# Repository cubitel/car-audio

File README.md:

Car Audio
=========

USB audio amplifier that turns android-based tablet into
full-featured automotive head unit.

#### Interfaces
- USB device interface for tablet
- USB host interface
- 4x45W digital class D automotive audio amplifier
- 2 CAN interfaces
- 100Base-T1 automotive ethernet interface
- Analog input for steering wheel keys
- FM radio available as separate shield

Amplifier acts as USB multifunctional device with ethernet and audio interfaces.

USB ethernet interface is used for configuration and control.
Interface has static IP address 192.168.91.11/24.

Hardware
--------

KiCad pcb files located in _pcb_ directory.
They include main amplifier board and FM tuner shield.

Software
--------

There is bootloader stub and main firmware.

#### Requirements

To install build tools in ubuntu:
```
sudo apt-get install gcc-arm-none-eabi dfu-util openssl protobuf-compiler python-protobuf
```

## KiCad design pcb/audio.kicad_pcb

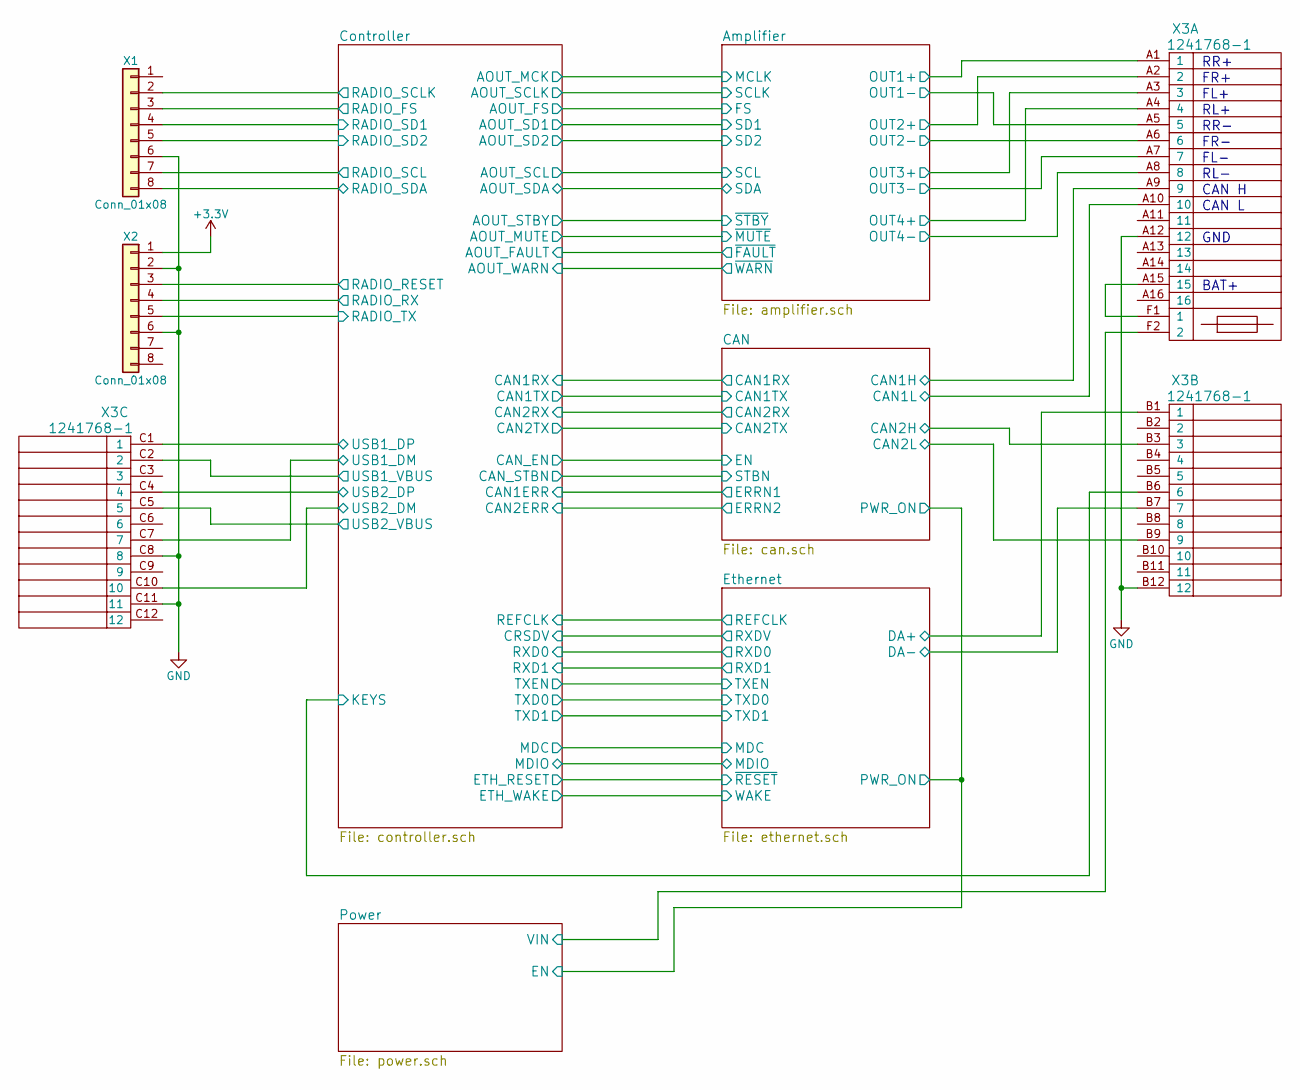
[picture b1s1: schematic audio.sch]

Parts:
X1, X2: Conn_01x08; Pin_Header_Straight_1x08_Pitch2.54mm
X3: 1241768-1; 1241768

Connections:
+3V3: X2.1; also elsewhere on the board
/Amplifier/OUT1+: X3.A1 (1); also elsewhere on the board
/Amplifier/OUT1-: X3.A5 (5); also elsewhere on the board
/Amplifier/OUT2+: X3.A2 (2); also elsewhere on the board
/Amplifier/OUT2-: X3.A6 (6); also elsewhere on the board
/Amplifier/OUT3+: X3.A3 (3); also elsewhere on the board
/Amplifier/OUT3-: X3.A7 (7); also elsewhere on the board
/Amplifier/OUT4+: X3.A4 (4); also elsewhere on the board
/Amplifier/OUT4-: X3.A8 (8); also elsewhere on the board
/CAN/CAN1H: X3.A9 (9); also elsewhere on the board
/CAN/CAN1L: X3.A10 (10); also elsewhere on the board
/CAN/CAN2H: X3.B3 (3); also elsewhere on the board
/CAN/CAN2L: X3.B9 (9); also elsewhere on the board
/Controller/KEYS: X3.B6 (6); also elsewhere on the board
/Controller/RADIO_FS: X1.3; also elsewhere on the board
/Controller/RADIO_RESET: X2.3; also elsewhere on the board
/Controller/RADIO_RX: X2.4; also elsewhere on the board
/Controller/RADIO_SCL: X1.7; also elsewhere on the board
/Controller/RADIO_SCLK: X1.2; also elsewhere on the board
/Controller/RADIO_SD1: X1.4; also elsewhere on the board
/Controller/RADIO_SD2: X1.5; also elsewhere on the board
/Controller/RADIO_SDA: X1.8; also elsewhere on the board
/Controller/RADIO_TX: X2.5; also elsewhere on the board
/Controller/USB1_DM: X3.C7 (7); also elsewhere on the board
/Controller/USB1_DP: X3.C1 (1); also elsewhere on the board
/Controller/USB1_VBUS: X3.C2 (2); also elsewhere on the board
/Controller/USB2_DM: X3.C10 (10); also elsewhere on the board
/Controller/USB2_DP: X3.C4 (4); also elsewhere on the board
/Controller/USB2_VBUS: X3.C5 (5); also elsewhere on the board
/Ethernet/DA+: X3.B1 (1); also elsewhere on the board
/Ethernet/DA-: X3.B7 (7); also elsewhere on the board
/Power/VIN: X3.F2 (2); also elsewhere on the board
GND: X1.6, X2.2, X2.6, X3.A12 (12), X3.B12 (12), X3.C8 (8), X3.C11 (11); also elsewhere on the board
unnamed: X3.A15 (15), X3.F1 (1)

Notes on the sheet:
RR+
FR+
FL+
RL+
RR-
FR-
FL-
RL-
GND
BAT+
CAN H
CAN L

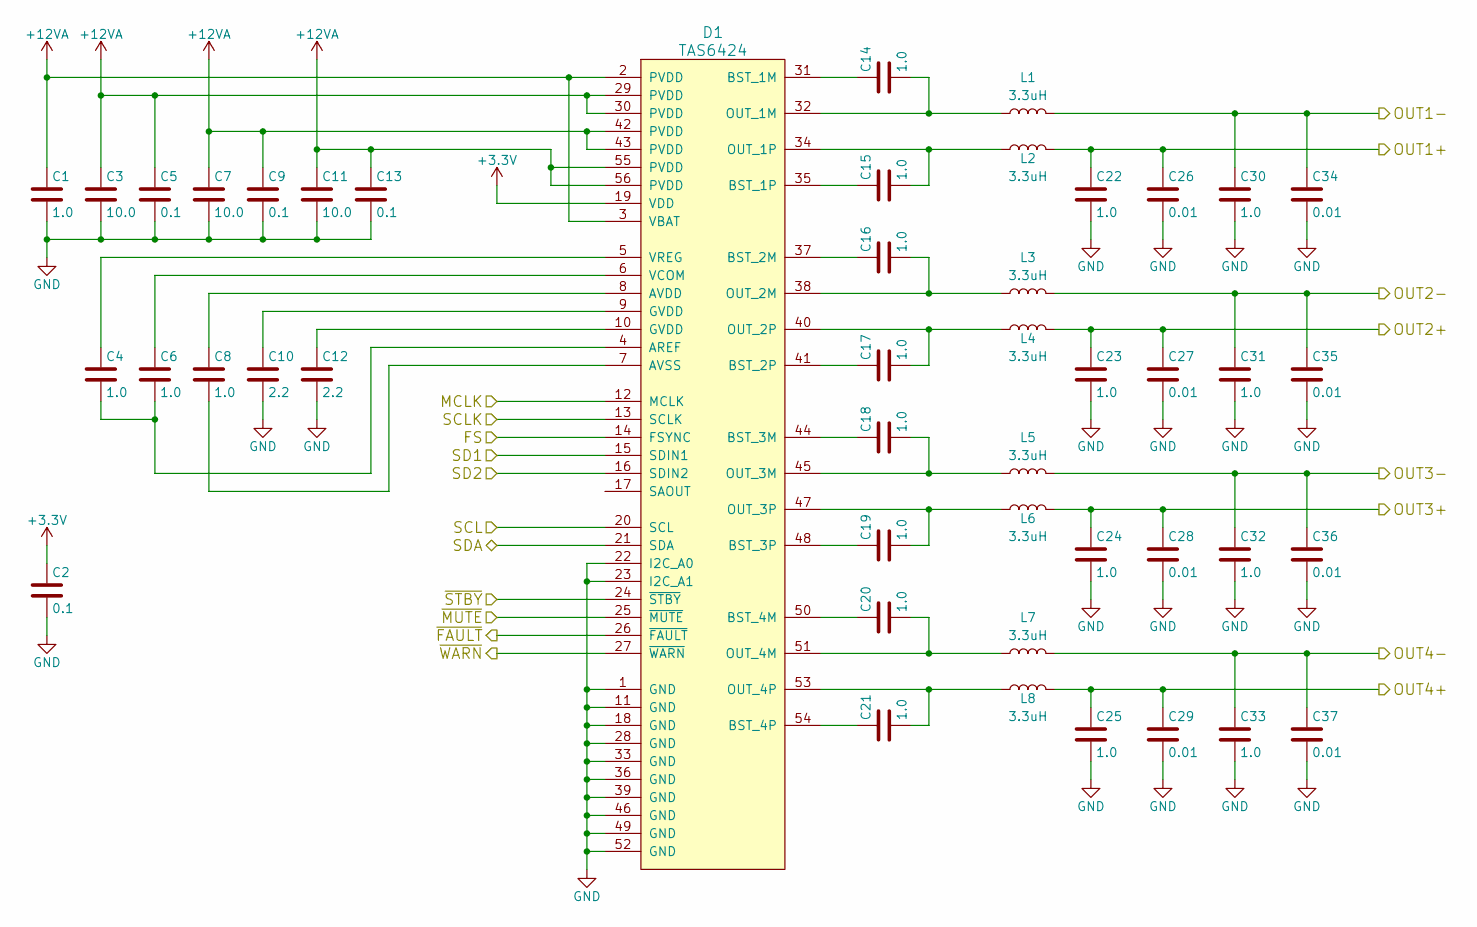
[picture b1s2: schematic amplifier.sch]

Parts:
C1, C22, C23, C24, C25, C30, C31, C32, C33: 1.0; C_0805
C2, C5, C9, C13: 0.1; C_0603
C3, C7, C11: 10.0; C_1210
C4, C6, C8, C14, C15, C16, C17, C18, C19, C20, C21: 1.0; C_0603
C10, C12: 2.2; C_0805
C26, C27, C28, C29, C34, C35, C36, C37: 0.01; C_0603
D1: TAS6424; SSOP-56_7.5x18.5mm_Pitch0.635mm
L1, L2, L3, L4, L5, L6, L7, L8: 3.3uH; L_10.4x10.4_H4.8

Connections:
+3V3: C2.1, D1.19 (VDD); also elsewhere on the board
+12VA: C1.1, C3.1, C5.1, C7.1, C9.1, C11.1, C13.1, D1.2 (PVDD), D1.3 (VBAT), D1.29 (PVDD), D1.30 (PVDD), D1.42 (PVDD), D1.43 (PVDD), D1.55 (PVDD), D1.56 (PVDD); also elsewhere on the board
/Amplifier/OUT1+: C22.1, C26.1, L2.2; also elsewhere on the board
/Amplifier/OUT1-: C30.1, C34.1, L1.2; also elsewhere on the board
/Amplifier/OUT2+: C23.1, C27.1, L4.2; also elsewhere on the board
/Amplifier/OUT2-: C31.1, C35.1, L3.2; also elsewhere on the board
/Amplifier/OUT3+: C24.1, C28.1, L6.2; also elsewhere on the board
/Amplifier/OUT3-: C32.1, C36.1, L5.2; also elsewhere on the board
/Amplifier/OUT4+: C25.1, C29.1, L8.2; also elsewhere on the board
/Amplifier/OUT4-: C33.1, C37.1, L7.2; also elsewhere on the board
/Controller/AOUT_FAULT: D1.26 (~FAULT); also elsewhere on the board
/Controller/AOUT_FS: D1.14 (FSYNC); also elsewhere on the board
/Controller/AOUT_MCK: D1.12 (MCLK); also elsewhere on the board
/Controller/AOUT_MUTE: D1.25 (~MUTE); also elsewhere on the board
/Controller/AOUT_SCL: D1.20 (SCL); also elsewhere on the board
/Controller/AOUT_SCLK: D1.13 (SCLK); also elsewhere on the board
/Controller/AOUT_SD1: D1.15 (SDIN1); also elsewhere on the board
/Controller/AOUT_SD2: D1.16 (SDIN2); also elsewhere on the board
/Controller/AOUT_SDA: D1.21 (SDA); also elsewhere on the board
/Controller/AOUT_STBY: D1.24 (~STBY); also elsewhere on the board
/Controller/AOUT_WARN: D1.27 (~WARN); also elsewhere on the board
GND: C1.2, C2.2, C3.2, C5.2, C7.2, C9.2, C10.2, C11.2, C12.2, C13.2, C22.2, C23.2, C24.2, C25.2, C26.2, C27.2, C28.2, C29.2, C30.2, C31.2, C32.2, C33.2, C34.2, C35.2, C36.2, C37.2, D1.1 (GND), D1.11 (GND), D1.18 (GND), D1.22 (I2C_A0), D1.23 (I2C_A1), D1.28 (GND), D1.33 (GND), D1.36 (GND), D1.39 (GND), D1.46 (GND), D1.49 (GND), D1.52 (GND); also elsewhere on the board
unnamed: C4.1, D1.5 (VREG)
unnamed: C4.2, C6.2, D1.4 (AREF)
unnamed: C6.1, D1.6 (VCOM)
unnamed: C8.1, D1.8 (AVDD)
unnamed: C8.2, D1.7 (AVSS)
unnamed: C10.1, D1.9 (GVDD)
unnamed: C12.1, D1.10 (GVDD)
unnamed: C14.1, D1.31 (BST_1M)
unnamed: C14.2, D1.32 (OUT_1M), L1.1
unnamed: C15.1, D1.35 (BST_1P)
unnamed: C15.2, D1.34 (OUT_1P), L2.1
unnamed: C16.1, D1.37 (BST_2M)
unnamed: C16.2, D1.38 (OUT_2M), L3.1
unnamed: C17.1, D1.41 (BST_2P)
unnamed: C17.2, D1.40 (OUT_2P), L4.1
unnamed: C18.1, D1.44 (BST_3M)
unnamed: C18.2, D1.45 (OUT_3M), L5.1
unnamed: C19.1, D1.48 (BST_3P)
unnamed: C19.2, D1.47 (OUT_3P), L6.1
unnamed: C20.1, D1.50 (BST_4M)
unnamed: C20.2, D1.51 (OUT_4M), L7.1
unnamed: C21.1, D1.54 (BST_4P)
unnamed: C21.2, D1.53 (OUT_4P), L8.1

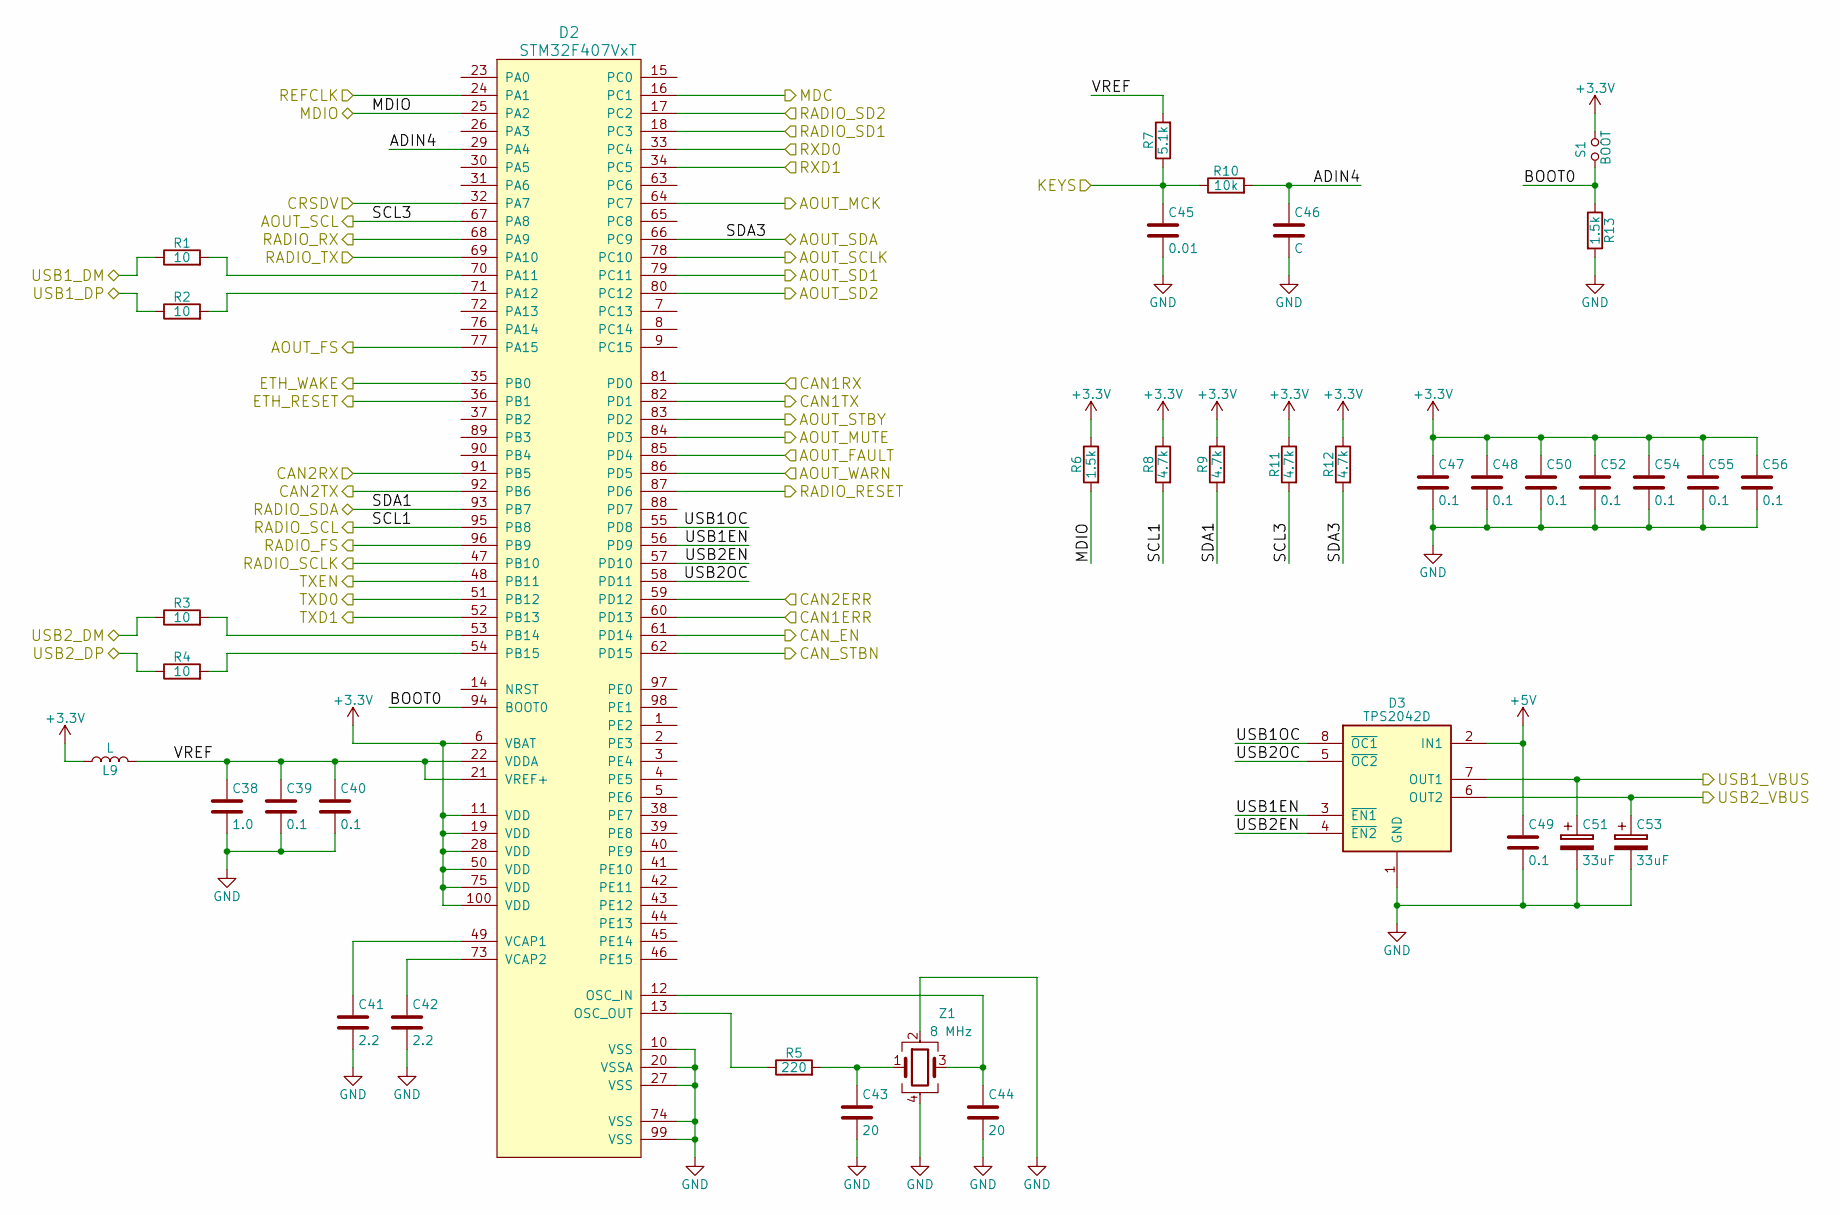
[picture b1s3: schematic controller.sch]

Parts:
C38: 1.0; C_0603
C39, C40, C47, C48, C49, C50, C52, C54, C55, C56: 0.1; C_0603
C41, C42: 2.2; C_0603
C43, C44: 20; C_0603
C45: 0.01; C_0603
C46: C; C_0603
C51, C53: 33uF; CP_Tantalum_Case-B_EIA-3528-21_Reflow
D2: STM32F407VxT; LQFP-100_14x14mm_Pitch0.5mm
D3: TPS2042D; SOIC-8_3.9x4.9mm_Pitch1.27mm
L9: L; L_0805
R1, R2, R3, R4: 10; R_0603
R5: 220; R_0603
R6, R13: 1.5k; R_0603
R7: 5.1k; R_0603
R8, R9, R11, R12: 4.7k; R_0603
R10: 10k; R_0603
S1: BOOT; Pin_Header_Straight_1x02_Pitch1.27mm
Z1: 8 MHz; Crystal_5x3

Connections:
+3V3: C47.1, C48.1, C50.1, C52.1, C54.1, C55.1, C56.1, D2.6 (VBAT), D2.11 (VDD), D2.19 (VDD), D2.28 (VDD), D2.50 (VDD), D2.75 (VDD), D2.100 (VDD), L9.1, R6.1, R8.1, R9.1, R11.1, R12.1, S1.2; also elsewhere on the board
+5V: C49.1, D3.2 (IN1); also elsewhere on the board
/CAN/CAN1RX: D2.81 (PD0); also elsewhere on the board
/CAN/CAN1TX: D2.82 (PD1); also elsewhere on the board
/CAN/CAN2RX: D2.91 (PB5); also elsewhere on the board
/CAN/CAN2TX: D2.92 (PB6); also elsewhere on the board
/Controller/ADIN4: C46.1, D2.29 (PA4), R10.2
/Controller/AOUT_FAULT: D2.85 (PD4); also elsewhere on the board
/Controller/AOUT_FS: D2.77 (PA15); also elsewhere on the board
/Controller/AOUT_MCK: D2.64 (PC7); also elsewhere on the board
/Controller/AOUT_MUTE: D2.84 (PD3); also elsewhere on the board
/Controller/AOUT_SCL: D2.67 (PA8), R11.2; also elsewhere on the board
/Controller/AOUT_SCLK: D2.78 (PC10); also elsewhere on the board
/Controller/AOUT_SD1: D2.79 (PC11); also elsewhere on the board
/Controller/AOUT_SD2: D2.80 (PC12); also elsewhere on the board
/Controller/AOUT_SDA: D2.66 (PC9), R12.2; also elsewhere on the board
/Controller/AOUT_STBY: D2.83 (PD2); also elsewhere on the board
/Controller/AOUT_WARN: D2.86 (PD5); also elsewhere on the board
/Controller/BOOT0: D2.94 (BOOT0), R13.1, S1.1
/Controller/CAN1ERR: D2.60 (PD13); also elsewhere on the board
/Controller/CAN2ERR: D2.59 (PD12); also elsewhere on the board
/Controller/CAN_EN: D2.61 (PD14); also elsewhere on the board
/Controller/CAN_STBN: D2.62 (PD15); also elsewhere on the board
/Controller/CRSDV: D2.32 (PA7); also elsewhere on the board
/Controller/ETH_RESET: D2.36 (PB1); also elsewhere on the board
/Controller/ETH_WAKE: D2.35 (PB0); also elsewhere on the board
/Controller/KEYS: C45.1, R7.1, R10.1; also elsewhere on the board
/Controller/MDC: D2.16 (PC1); also elsewhere on the board
/Controller/MDIO: D2.25 (PA2), R6.2; also elsewhere on the board
/Controller/RADIO_FS: D2.96 (PB9); also elsewhere on the board
/Controller/RADIO_RESET: D2.87 (PD6); also elsewhere on the board
/Controller/RADIO_RX: D2.68 (PA9); also elsewhere on the board
/Controller/RADIO_SCL: D2.95 (PB8), R8.2; also elsewhere on the board
/Controller/RADIO_SCLK: D2.47 (PB10); also elsewhere on the board
/Controller/RADIO_SD1: D2.18 (PC3); also elsewhere on the board
/Controller/RADIO_SD2: D2.17 (PC2); also elsewhere on the board
/Controller/RADIO_SDA: D2.93 (PB7), R9.2; also elsewhere on the board
/Controller/RADIO_TX: D2.69 (PA10); also elsewhere on the board
/Controller/REFCLK: D2.24 (PA1); also elsewhere on the board
/Controller/RXD0: D2.33 (PC4); also elsewhere on the board
/Controller/RXD1: D2.34 (PC5); also elsewhere on the board
/Controller/TXD0: D2.51 (PB12); also elsewhere on the board
/Controller/TXD1: D2.52 (PB13); also elsewhere on the board
/Controller/TXEN: D2.48 (PB11); also elsewhere on the board
/Controller/USB1EN: D2.56 (PD9), D3.3 (~EN1)
/Controller/USB1OC: D2.55 (PD8), D3.8 (~OC1)
/Controller/USB1_DM: R1.1; also elsewhere on the board
/Controller/USB1_DP: R2.1; also elsewhere on the board
/Controller/USB1_VBUS: C51.1, D3.7 (OUT1); also elsewhere on the board
/Controller/USB2EN: D2.57 (PD10), D3.4 (~EN2)
/Controller/USB2OC: D2.58 (PD11), D3.5 (~OC2)
/Controller/USB2_DM: R3.1; also elsewhere on the board
/Controller/USB2_DP: R4.1; also elsewhere on the board
/Controller/USB2_VBUS: C53.1, D3.6 (OUT2); also elsewhere on the board
/Controller/VREF: C38.1, C39.1, C40.1, D2.21 (VREF+), D2.22 (VDDA), L9.2, R7.2
GND: C38.2, C39.2, C40.2, C41.2, C42.2, C43.2, C44.2, C45.2, C46.2, C47.2, C48.2, C49.2, C50.2, C51.2, C52.2, C53.2, C54.2, C55.2, C56.2, D2.10 (VSS), D2.20 (VSSA), D2.27 (VSS), D2.74 (VSS), D2.99 (VSS), D3.1 (GND), R13.2, Z1.2, Z1.4; also elsewhere on the board
unnamed: C41.1, D2.49 (VCAP1)
unnamed: C42.1, D2.73 (VCAP2)
unnamed: C43.1, R5.2, Z1.1
unnamed: C44.1, D2.12 (OSC_IN), Z1.3
unnamed: D2.13 (OSC_OUT), R5.1
unnamed: D2.53 (PB14), R3.2
unnamed: D2.54 (PB15), R4.2
unnamed: D2.70 (PA11), R1.2
unnamed: D2.71 (PA12), R2.2

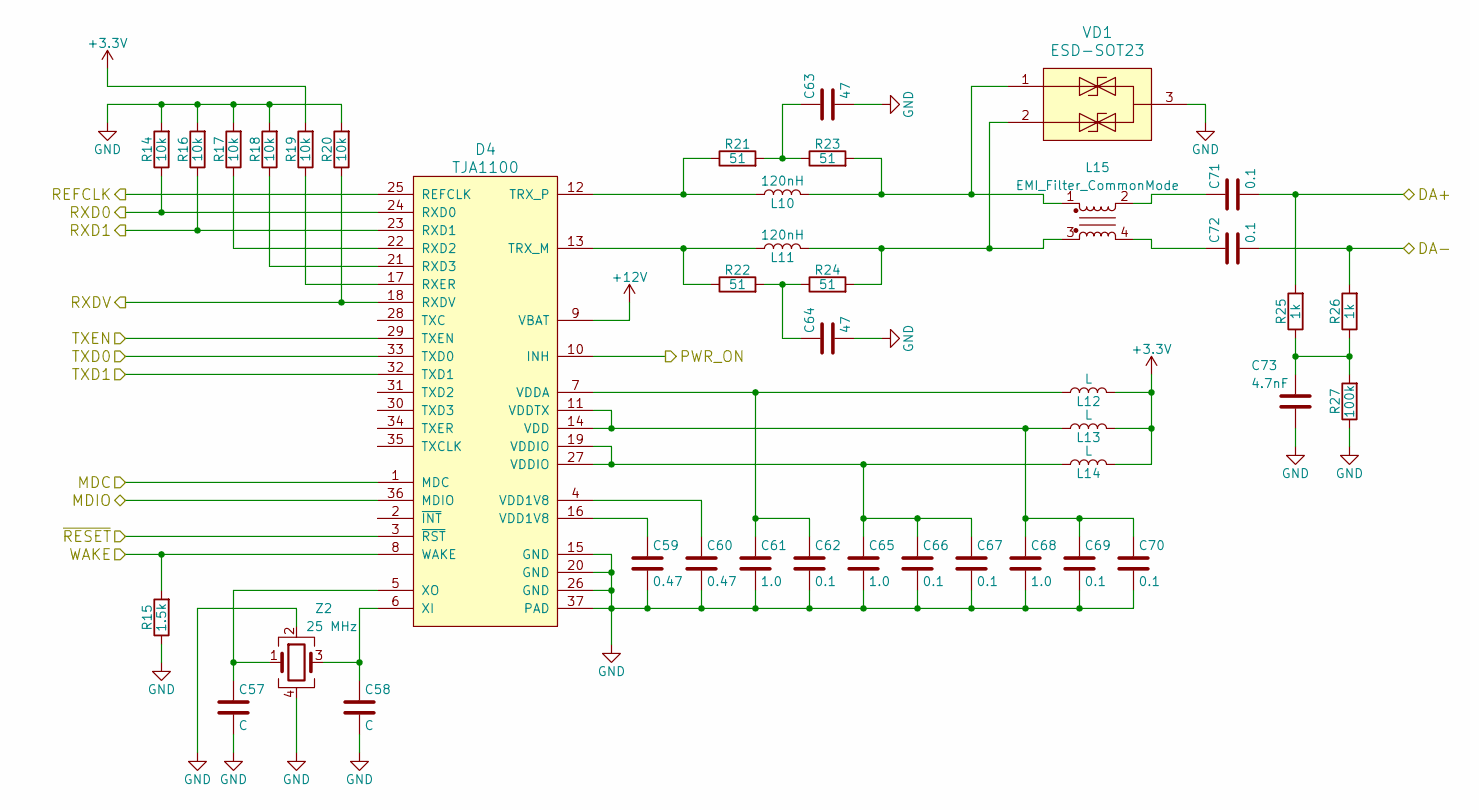
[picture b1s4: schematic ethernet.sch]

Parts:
C57, C58: C; C_0603
C59, C60: 0.47; C_0603
C61, C65, C68: 1.0; C_0603
C62, C66, C67, C69, C70, C71, C72: 0.1; C_0603
C63, C64: 47; C_0603
C73: 4.7nF; C_0603
D4: TJA1100; QFN-36-1EP_6x6mm_Pitch0.5mm
L10, L11: 120nH; L_0805
L12, L13, L14: L; L_0805
L15: EMI_Filter_CommonMode; SIMDAD 1812
R14, R16, R17, R18, R19, R20: 10k; R_0603
R15: 1.5k; R_0603
R21, R22, R23, R24: 51; R_0603
R25, R26: 1k; R_0603
R27: 100k; R_0603
VD1: ESD-SOT23; SOT-23
Z2: 25 MHz; Crystal_5x3

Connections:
+3V3: L12.2, L13.2, L14.2, R19.2; also elsewhere on the board
+12V: D4.9 (VBAT); also elsewhere on the board
/Controller/CRSDV: D4.18 (RXDV), R20.1; also elsewhere on the board
/Controller/ETH_RESET: D4.3 (~RST); also elsewhere on the board
/Controller/ETH_WAKE: D4.8 (WAKE), R15.2; also elsewhere on the board
/Controller/MDC: D4.1 (MDC); also elsewhere on the board
/Controller/MDIO: D4.36 (MDIO); also elsewhere on the board
/Controller/REFCLK: D4.25 (REFCLK); also elsewhere on the board
/Controller/RXD0: D4.24 (RXD0), R14.1; also elsewhere on the board
/Controller/RXD1: D4.23 (RXD1), R16.1; also elsewhere on the board
/Controller/TXD0: D4.33 (TXD0); also elsewhere on the board
/Controller/TXD1: D4.32 (TXD1); also elsewhere on the board
/Controller/TXEN: D4.29 (TXEN); also elsewhere on the board
/Ethernet/DA+: C71.2, R25.2; also elsewhere on the board
/Ethernet/DA-: C72.2, R26.2; also elsewhere on the board
/Power/EN: D4.10 (INH); also elsewhere on the board
GND: C57.2, C58.2, C59.2, C60.2, C61.2, C62.2, C63.2, C64.2, C65.2, C66.2, C67.2, C68.2, C69.2, C70.2, C73.2, D4.15 (GND), D4.20 (GND), D4.26 (GND), D4.37 (PAD), R14.2, R15.1, R16.2, R17.2, R18.2, R20.2, R27.1, VD1.3, Z2.2, Z2.4; also elsewhere on the board
unnamed: C57.1, D4.5 (XO), Z2.1
unnamed: C58.1, D4.6 (XI), Z2.3
unnamed: C59.1, D4.16 (VDD1V8)
unnamed: C60.1, D4.4 (VDD1V8)
unnamed: C61.1, C62.1, D4.7 (VDDA), L12.1
unnamed: C63.1, R21.2, R23.1
unnamed: C64.1, R22.2, R24.1
unnamed: C65.1, C66.1, C67.1, D4.19 (VDDIO), D4.27 (VDDIO), L14.1
unnamed: C68.1, C69.1, C70.1, D4.11 (VDDTX), D4.14 (VDD), L13.1
unnamed: C71.1, L15.2
unnamed: C72.1, L15.4
unnamed: C73.1, R25.1, R26.1, R27.2
unnamed: D4.12 (TRX_P), L10.1, R21.1
unnamed: D4.13 (TRX_M), L11.1, R22.1
unnamed: D4.17 (RXER), R19.1
unnamed: D4.21 (RXD3), R18.1
unnamed: D4.22 (RXD2), R17.1
unnamed: L10.2, L15.1, R23.2, VD1.1
unnamed: L11.2, L15.3, R24.2, VD1.2

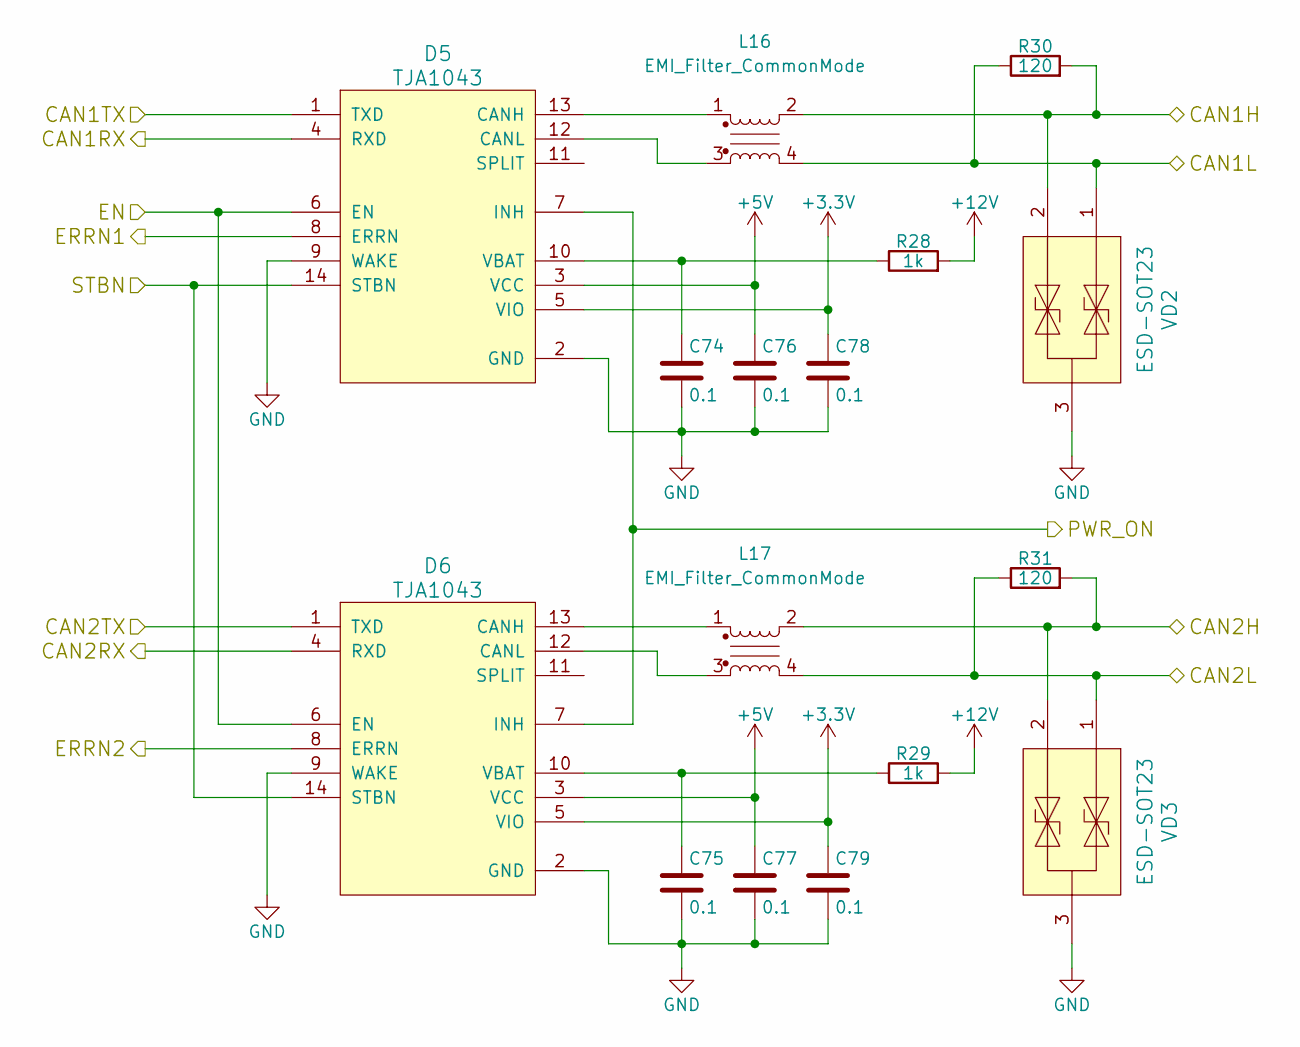
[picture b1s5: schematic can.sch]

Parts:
C74, C75, C76, C77, C78, C79: 0.1; C_0603
D5, D6: TJA1043; SOIC-14_3.9x8.7mm_Pitch1.27mm
L16, L17: EMI_Filter_CommonMode; SIMDAD 1812
R28, R29: 1k; R_0603
R30, R31: 120; R_0603
VD2, VD3: ESD-SOT23; SOT-23

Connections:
+3V3: C78.1, C79.1, D5.5 (VIO), D6.5 (VIO); also elsewhere on the board
+5V: C76.1, C77.1, D5.3 (VCC), D6.3 (VCC); also elsewhere on the board
+12V: R28.2, R29.2; also elsewhere on the board
/CAN/CAN1H: L16.2, R30.2, VD2.2; also elsewhere on the board
/CAN/CAN1L: L16.4, R30.1, VD2.1; also elsewhere on the board
/CAN/CAN1RX: D5.4 (RXD); also elsewhere on the board
/CAN/CAN1TX: D5.1 (TXD); also elsewhere on the board
/CAN/CAN2H: L17.2, R31.2, VD3.2; also elsewhere on the board
/CAN/CAN2L: L17.4, R31.1, VD3.1; also elsewhere on the board
/CAN/CAN2RX: D6.4 (RXD); also elsewhere on the board
/CAN/CAN2TX: D6.1 (TXD); also elsewhere on the board
/Controller/CAN1ERR: D5.8 (ERRN); also elsewhere on the board
/Controller/CAN2ERR: D6.8 (ERRN); also elsewhere on the board
/Controller/CAN_EN: D5.6 (EN), D6.6 (EN); also elsewhere on the board
/Controller/CAN_STBN: D5.14 (STBN), D6.14 (STBN); also elsewhere on the board
/Power/EN: D5.7 (INH), D6.7 (INH); also elsewhere on the board
GND: C74.2, C75.2, C76.2, C77.2, C78.2, C79.2, D5.2 (GND), D5.9 (WAKE), D6.2 (GND), D6.9 (WAKE), VD2.3, VD3.3; also elsewhere on the board
unnamed: C74.1, D5.10 (VBAT), R28.1
unnamed: C75.1, D6.10 (VBAT), R29.1
unnamed: D5.12 (CANL), L16.3
unnamed: D5.13 (CANH), L16.1
unnamed: D6.12 (CANL), L17.3
unnamed: D6.13 (CANH), L17.1

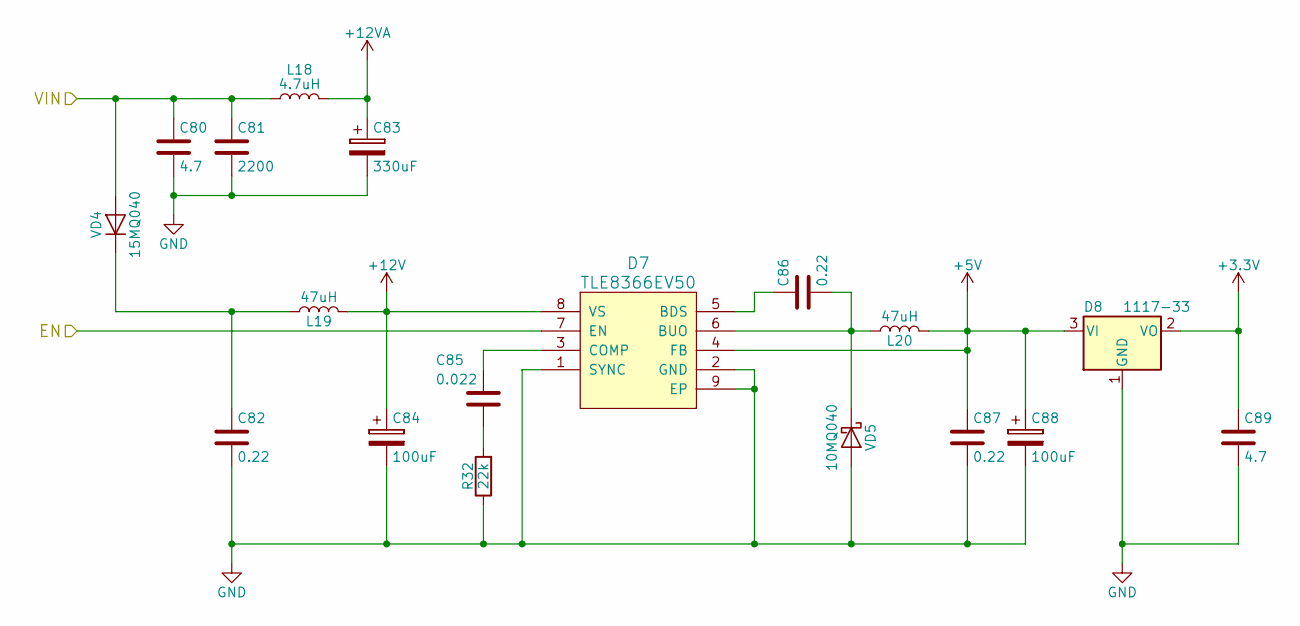
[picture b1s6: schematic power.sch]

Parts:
C80: 4.7; C_1206
C81: 2200; C_0603
C82: 0.22; C_0805
C83: 330uF; CP_Elec_10x10.5
C84: 100uF; CP_Elec_10x10.5
C85: 0.022; C_0603
C86, C87: 0.22; C_0603
C88: 100uF; CP_Tantalum_Case-D_EIA-7343-31_Reflow
C89: 4.7; C_0603
D7: TLE8366EV50; SOIC-8-1EP_3.9x4.9mm_Pitch1.27mm
D8: 1117-33; SOT-223-3_TabPin2
L18: 4.7uH; L_10.4x10.4_H4.8
L19, L20: 47uH; L_12x12mm_h8mm
R32: 22k; R_0603
VD4: 15MQ040; D_SMA
VD5: 10MQ040; D_SMA

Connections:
+3V3: C89.1, D8.2 (VO); also elsewhere on the board
+5V: C87.1, C88.1, D7.4 (FB), D8.3 (VI), L20.2; also elsewhere on the board
+12V: C84.1, D7.8 (VS), L19.2; also elsewhere on the board
+12VA: C83.1, L18.2; also elsewhere on the board
/Power/EN: D7.7 (EN); also elsewhere on the board
/Power/VIN: C80.1, C81.1, L18.1, VD4.2 (A); also elsewhere on the board
GND: C80.2, C81.2, C82.2, C83.2, C84.2, C87.2, C88.2, C89.2, D7.1 (SYNC), D7.2 (GND), D7.9 (EP), D8.1 (GND), R32.1, VD5.2 (A); also elsewhere on the board
unnamed: C82.1, L19.1, VD4.1 (K)
unnamed: C85.1, D7.3 (COMP)
unnamed: C85.2, R32.2
unnamed: C86.1, D7.5 (BDS)
unnamed: C86.2, D7.6 (BUO), L20.1, VD5.1 (K)

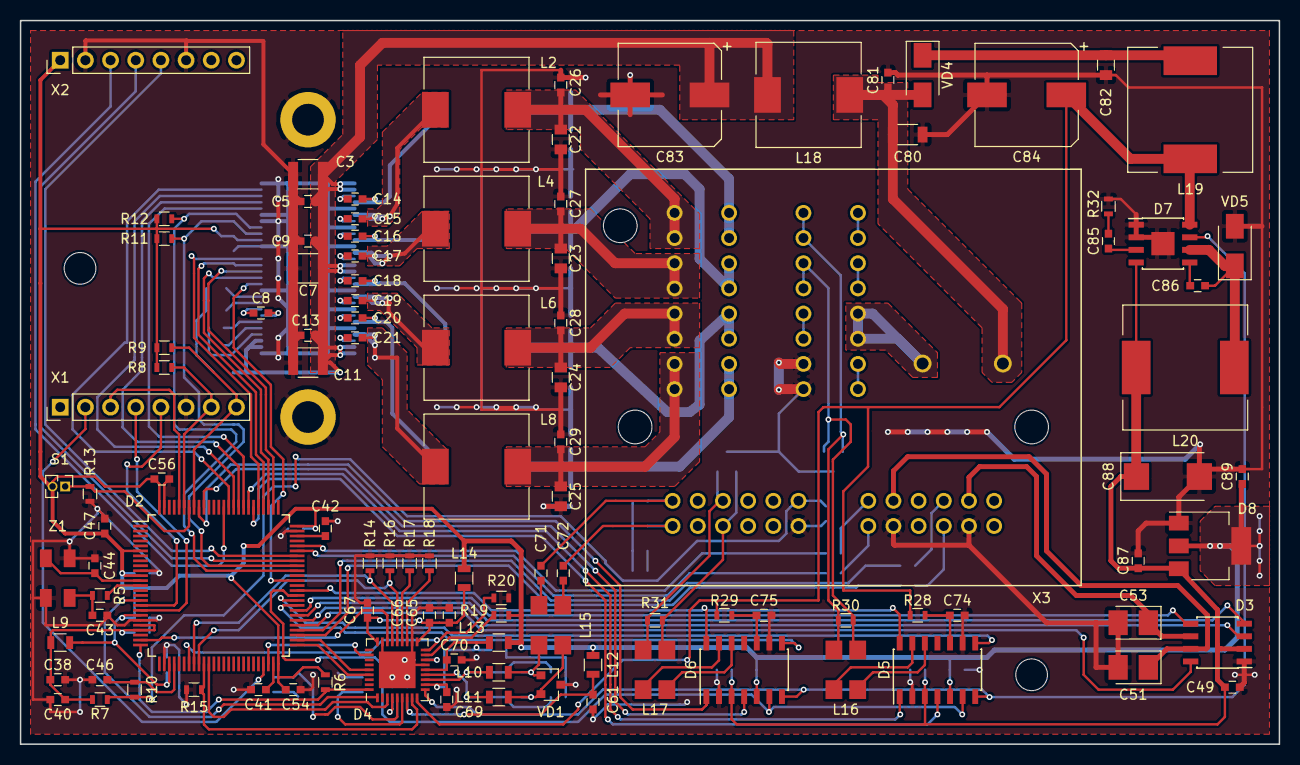
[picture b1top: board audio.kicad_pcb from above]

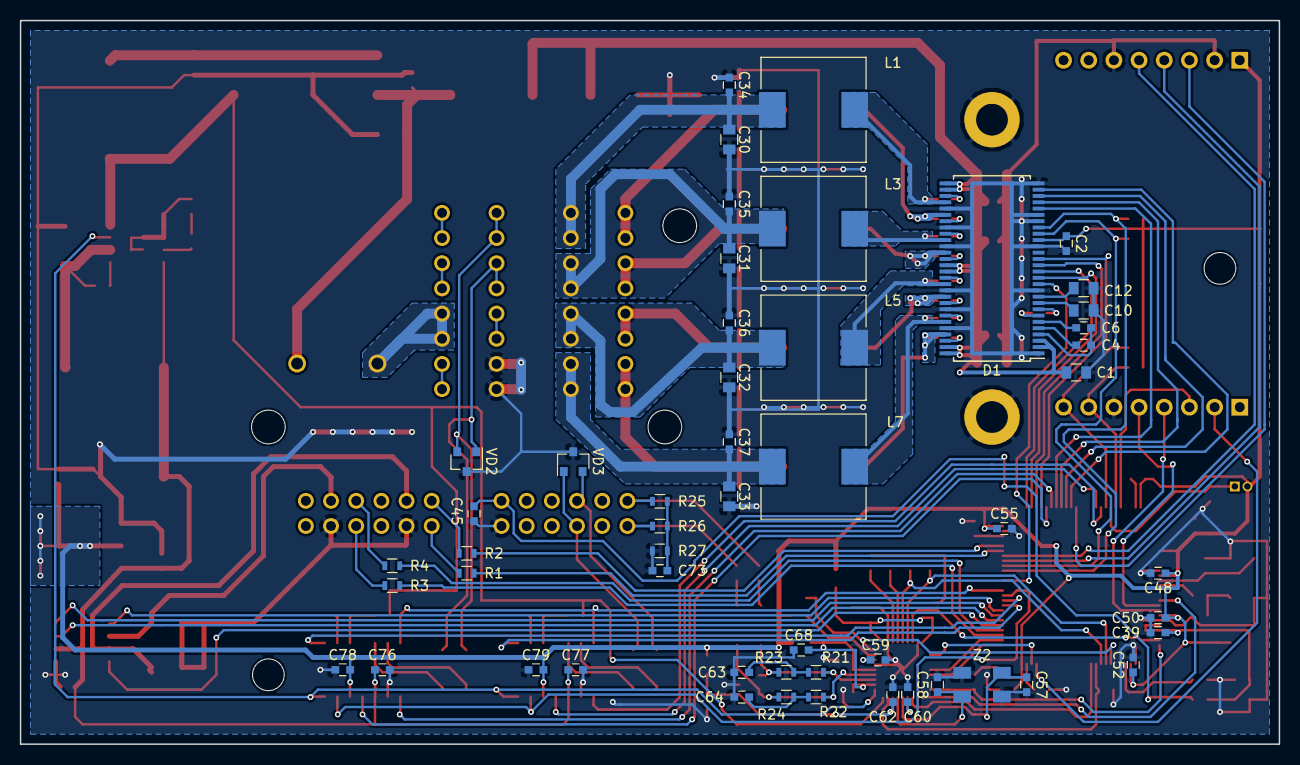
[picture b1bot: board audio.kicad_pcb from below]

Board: 2 copper layers, 127.0 x 73.0 mm, 160 parts (52 on the bottom side), 137 nets.

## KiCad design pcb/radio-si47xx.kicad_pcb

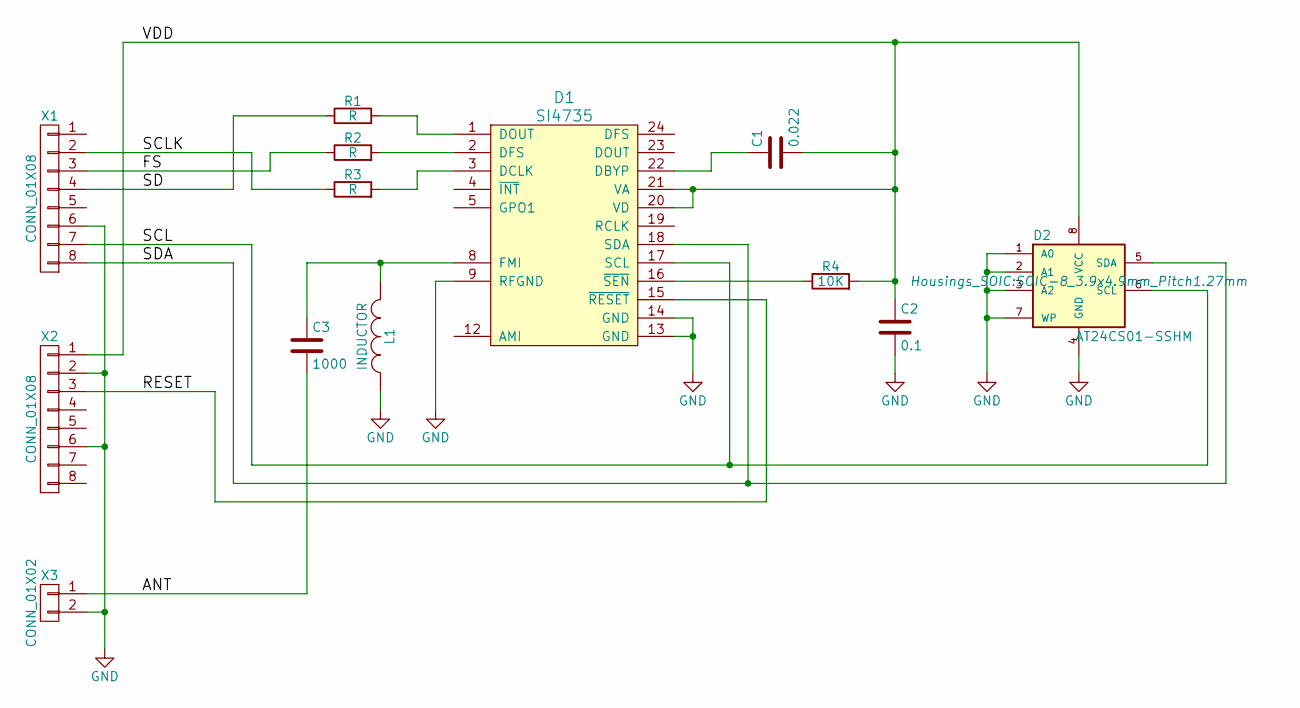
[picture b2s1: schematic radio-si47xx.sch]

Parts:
C1: 0.022; C_0603
C2: 0.1; C_0603
C3: 1000; C_0603
D1: SI4735; SSOP-24_3.9x8.7mm_Pitch0.635mm
D2: AT24CS01-SSHM; SOIC-8_3.9x4.9mm_Pitch1.27mm
L1: INDUCTOR; R_0603
R1, R2, R3: R; R_0603
R4: 10K; R_0603
X1, X2: CONN_01X08; Socket_Strip_Straight_1x08
X3: CONN_01X02; F_CONNECTOR

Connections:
/ANT: C3.2, X3.1
/FS: R2.1, X1.3
/RESET: D1.15 (~RESET), X2.3
/SCL: D1.17 (SCL), D2.6 (SCL), X1.7
/SCLK: R3.1, X1.2
/SD: R1.1, X1.4
/SDA: D1.18 (SDA), D2.5 (SDA), X1.8
/VDD: C1.2, C2.1, D1.20 (VD), D1.21 (VA), D2.8 (VCC), R4.2, X2.1
GND: C2.2, D1.9 (RFGND), D1.13 (GND), D1.14 (GND), D2.1 (A0), D2.2 (A1), D2.3 (A2), D2.4 (GND), D2.7 (WP), L1.1, X1.6, X2.2, X2.6, X3.2
unnamed: C1.1, D1.22 (DBYP)
unnamed: C3.1, D1.8 (FMI), L1.2
unnamed: D1.1 (DOUT), R1.2
unnamed: D1.2 (DFS), R2.2
unnamed: D1.3 (DCLK), R3.2
unnamed: D1.16 (~SEN), R4.1

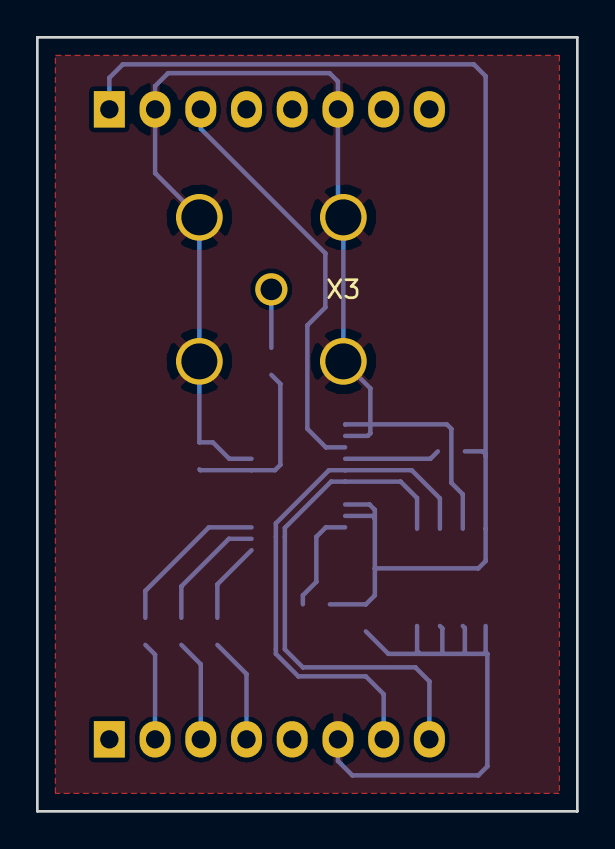
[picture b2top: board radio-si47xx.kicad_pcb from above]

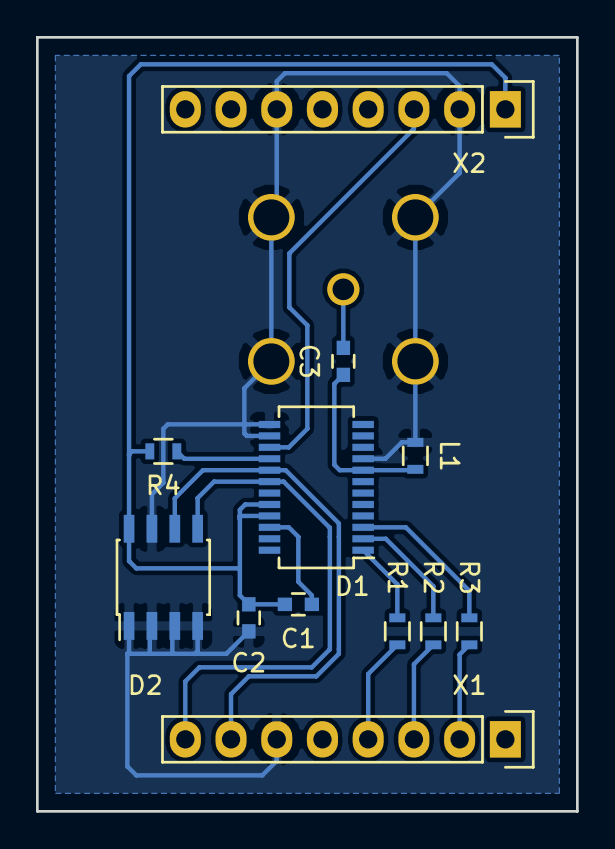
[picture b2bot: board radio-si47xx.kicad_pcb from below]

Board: 2 copper layers, 30.0 x 43.0 mm, 13 parts (12 on the bottom side), 15 nets.

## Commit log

2019-02-07 Added boot cause and exception address logging
2019-02-12 Added CAN input queue. Added Mercedes W164 support.
